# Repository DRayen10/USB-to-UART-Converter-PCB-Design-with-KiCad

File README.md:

# 🔌 USB to UART Converter PCB Design (KiCad)

## 📌 Overview
This project presents a custom-designed USB to UART Converter PCB developed using KiCad. It enables seamless communication between a computer and microcontrollers by converting USB signals into UART (serial) signals.

The board is ideal for programming, debugging, and interfacing embedded systems.

---

## ⚙️ Features
- ✅ USB to UART signal conversion  
- ✅ Reliable serial communication  
- ✅ Compact and optimized PCB layout  
- ✅ Supports standard TX/RX interface  
- ✅ Plug-and-play functionality  

---

## 🧠 How It Works
The USB to UART converter acts as a bridge between a computer and a microcontroller:
- The computer sends data via USB  
- The converter chip translates it into UART signals (TX/RX)  
- The microcontroller receives and processes the data  

This also works in reverse for serial monitoring and debugging.

---

## 🔌 Hardware Components
- USB to UART IC (e.g., CH340, CP2102, or FT232RL)  
- USB connector (Micro USB / Type-C)  
- Crystal oscillator (if required by IC)  
- Capacitors and resistors  
- TX/RX header pins  
- Power indicators (LEDs)  

---

## 🖥️ PCB Design
- Designed using **KiCad**
- Includes:
  - Schematic design  
  - PCB layout  
  - 3D visualization  
- Optimized routing for signal integrity and compact size  

---

---

## 📸 Preview
Add screenshots of:
- Schematic  
- PCB layout  
- 3D render  

---

## 🚀 Applications
- Microcontroller programming  
- Serial debugging  
- Embedded systems development  
- IoT prototyping  

---

## ⚠️ Notes
- Ensure correct TX/RX cross connection:
  - TX → RX  
  - RX → TX  
- Verify voltage levels (3.3V vs 5V compatibility)

---

## 🛠️ Tools Used
- KiCad (PCB Design)
- Standard electronic components

---

## 📬 Author
**Your Name**  
Embedded Systems & PCB Design Enthusiast  

---

## ⭐ Contribution
Contributions, suggestions, and improvements are welcome! Feel free to fork this project and enhance it.

---

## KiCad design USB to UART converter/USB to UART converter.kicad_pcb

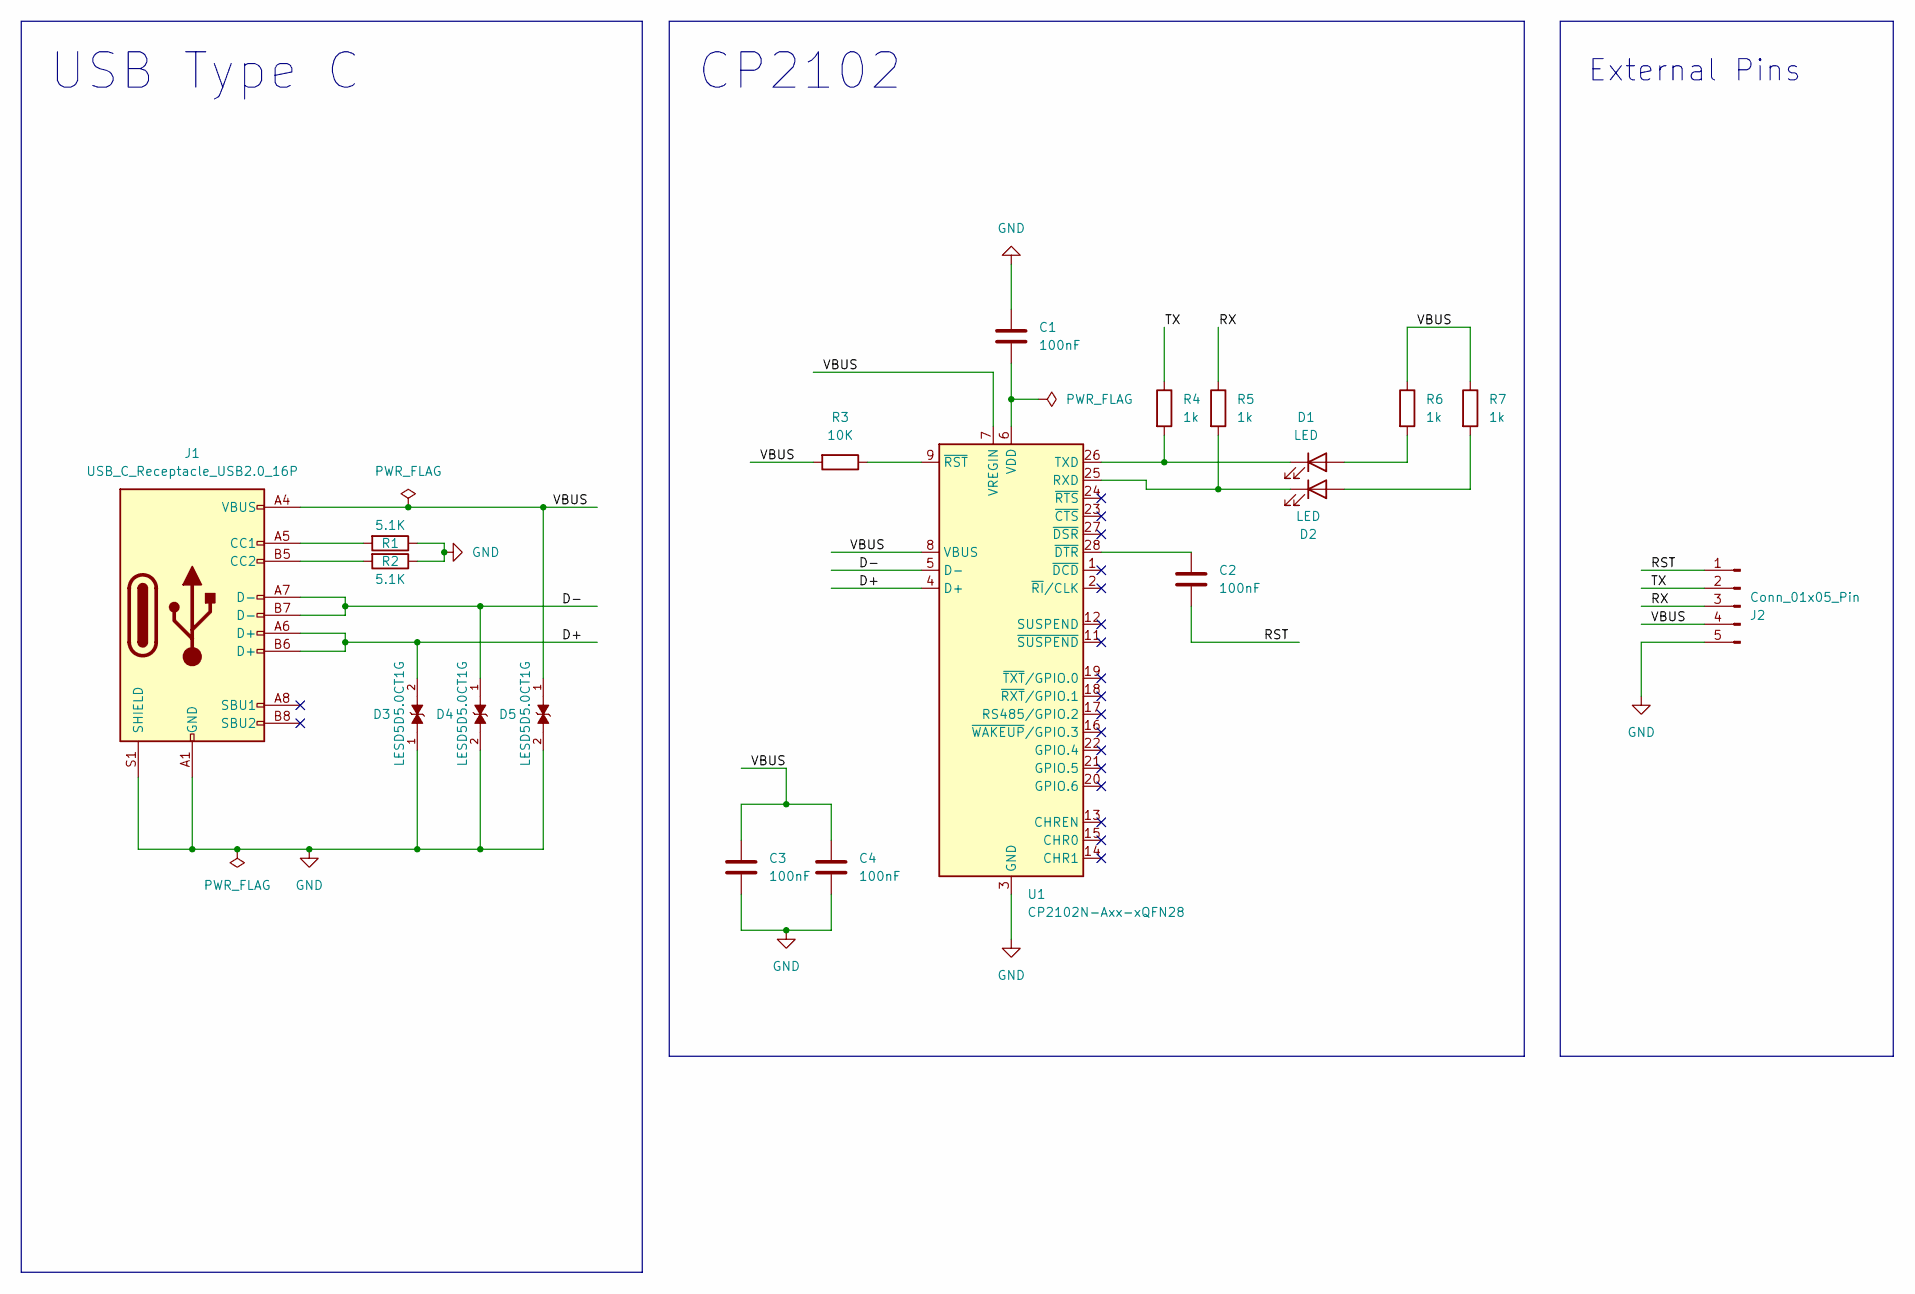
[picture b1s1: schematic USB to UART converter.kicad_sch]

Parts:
C1, C2, C3, C4: 100nF; C_0201_0603Metric
D1, D2: LED; LED_0201_0603Metric
D3, D4, D5: LESD5D5.0CT1G; TVS_LESD5D5.0CT1G; PARTREV O
J1: USB_C_Receptacle_USB2.0_16P; USB_C_Receptacle_HRO_TYPE-C-31-M-12
J2: Conn_01x05_Pin; PinHeader_1x05_P2.54mm_Horizontal
R1, R2: 5.1K; R_0201_0603Metric
R3: 10K; R_0201_0603Metric
R4, R5, R6, R7: 1k; R_0201_0603Metric
U1: CP2102N-Axx-xQFN28; QFN-28-1EP_5x5mm_P0.5mm_EP3.35x3.35mm

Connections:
/D+: D3.2, J1.A6 (D+), J1.B6 (D+), U1.4 (D+)
/D-: D4.1, J1.A7 (D-), J1.B7 (D-), U1.5 (D-)
/RST: C2.2, J2.1
/RX: J2.3, R5.1
/TX: J2.2, R4.1
/VBUS: C3.1, C4.1, D5.1, J1.A4 (VBUS), J1.A9 (VBUS), J1.B4 (VBUS), J1.B9 (VBUS), J2.4, R3.2, R6.1, R7.1, U1.7 (VREGIN), U1.8 (VBUS)
GND: C1.1, C3.2, C4.2, D3.1, D4.2, D5.2, J1.A1 (GND), J1.A12 (GND), J1.B1 (GND), J1.B12 (GND), J1.S1 (SHIELD), J2.5, R1.1, R2.1, U1.3 (GND), U1.29 (GND)
unnamed: D1.2 (A), R6.2
unnamed: D1.1 (K), R4.2, U1.26 (TXD)
unnamed: D2.2 (A), R7.2
unnamed: D2.1 (K), R5.2, U1.25 (RXD)
unnamed: J1.A5 (CC1), R1.2
unnamed: J1.B5 (CC2), R2.2
unnamed: C1.2, U1.6 (VDD)
unnamed: C2.1, U1.28 (~DTR)
unnamed: R3.1, U1.9 (~RST)

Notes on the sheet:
USB Type C
CP2102
External Pins

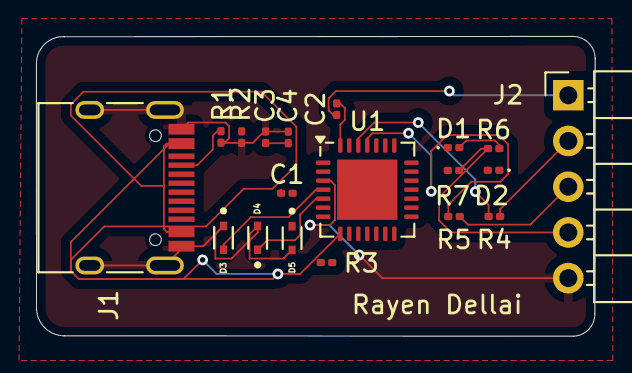
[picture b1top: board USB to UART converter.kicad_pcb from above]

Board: 2 copper layers, 31.0 x 16.7 mm, 19 parts (0 on the bottom side), 16 nets.
